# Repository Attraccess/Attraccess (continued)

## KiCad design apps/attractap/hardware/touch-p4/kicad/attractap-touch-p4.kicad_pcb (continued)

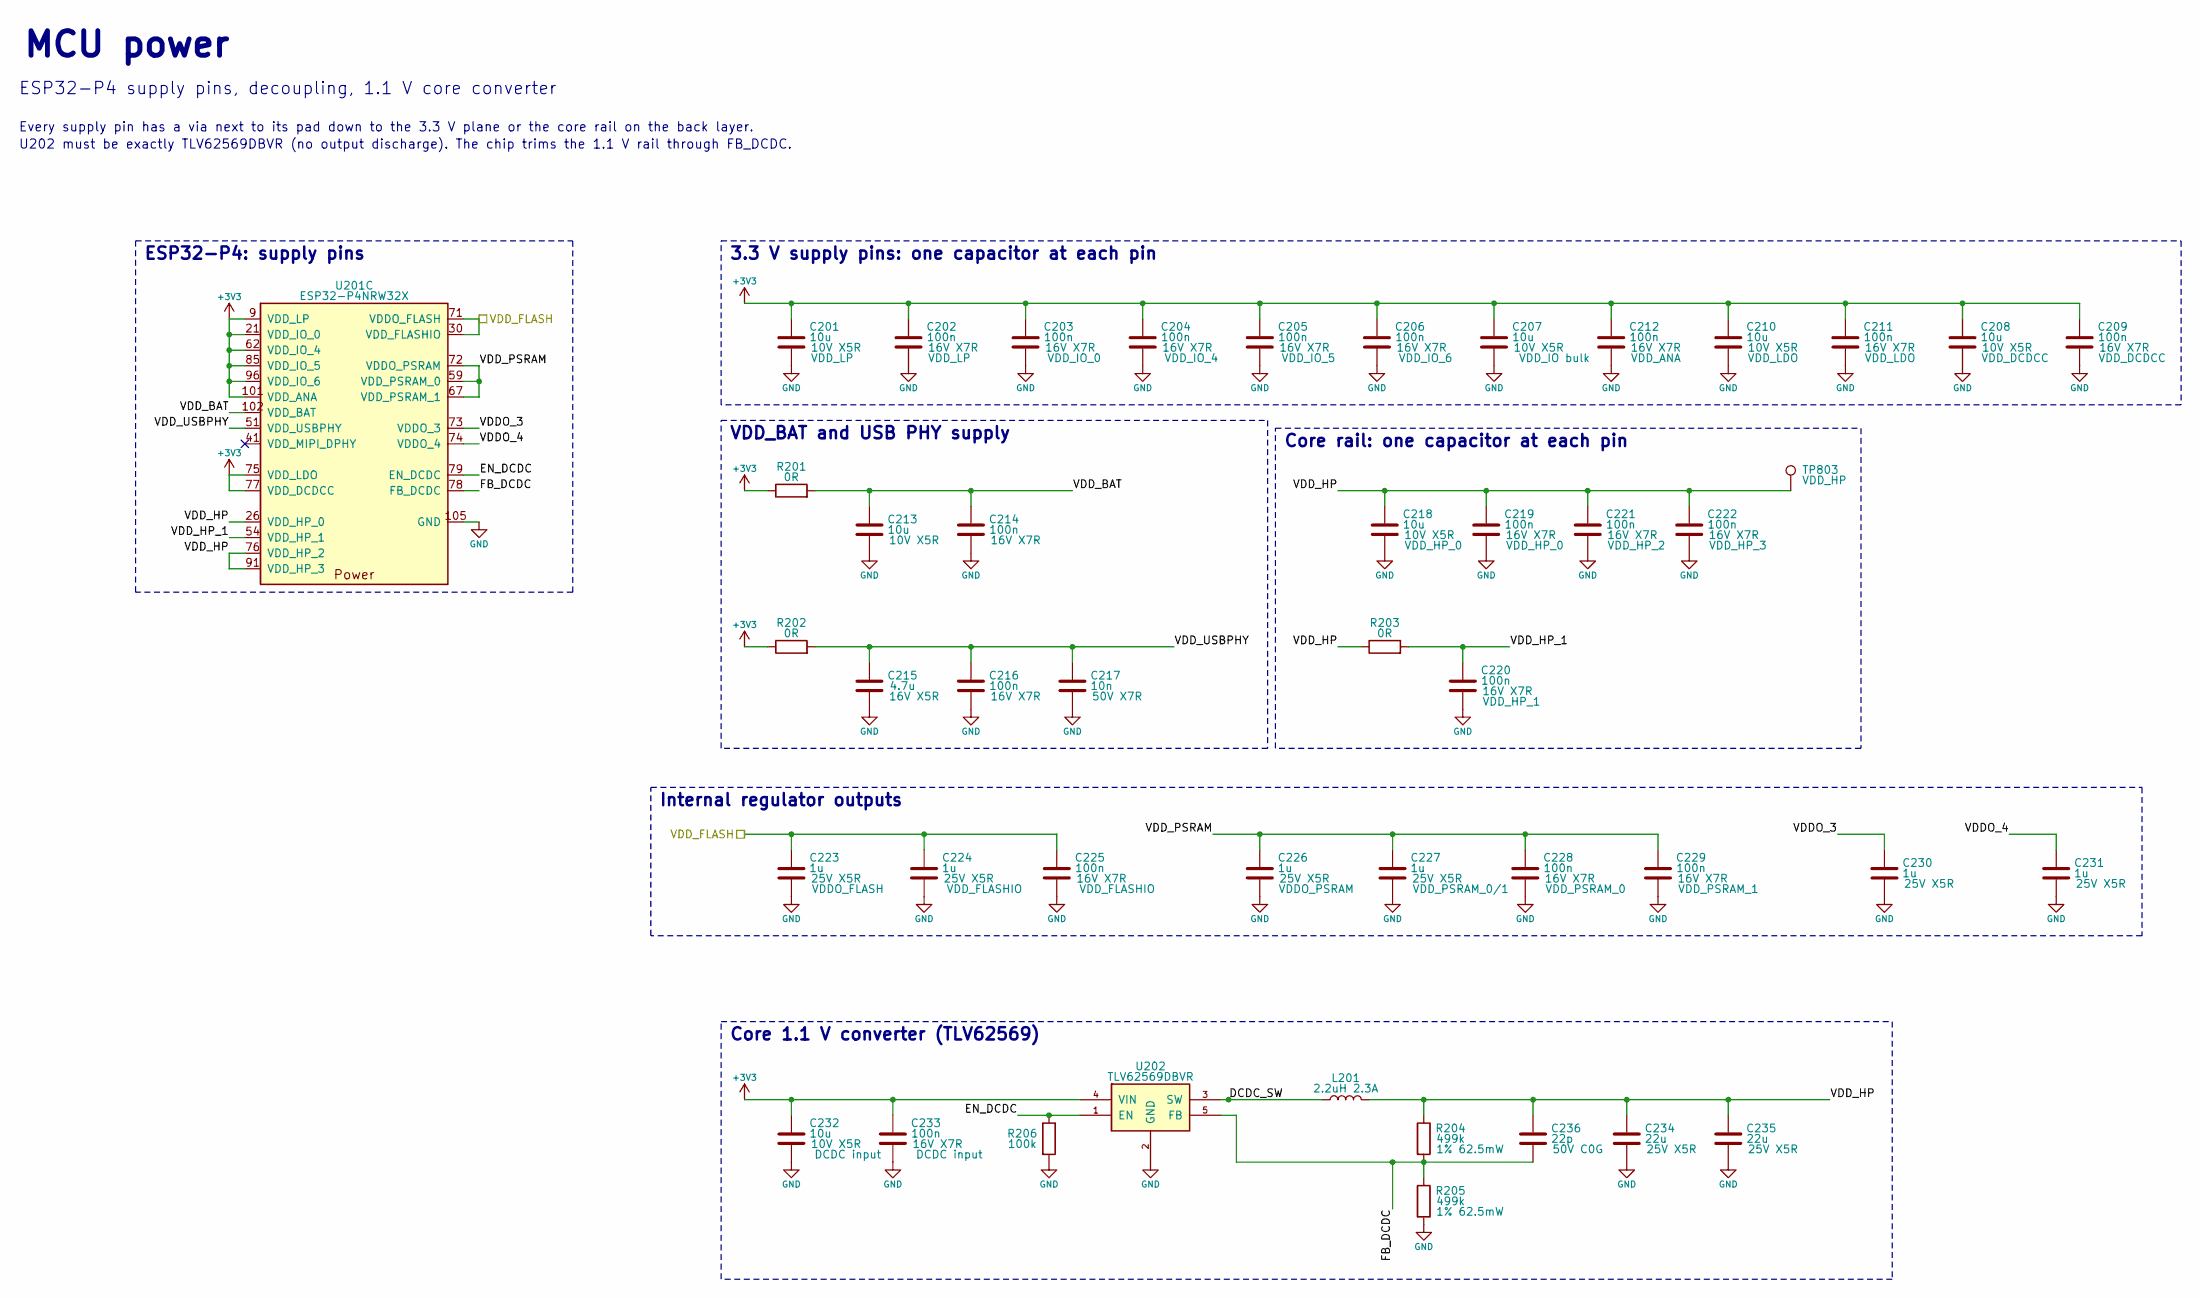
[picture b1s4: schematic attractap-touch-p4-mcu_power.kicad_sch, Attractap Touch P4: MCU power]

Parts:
C201, C207, C208, C210, C213, C218, C232: 10u; C_0603_1608Metric; Rating 10V X5R; MPN CL10A106KP8NNNC; LCSC C19702
C202, C203, C204, C205, C206, C209, C211, C212, C214, C216, C219, C220, C221, C222, C225, C228, C229, C233: 100n; C_0402_1005Metric; Rating 16V X7R; MPN CL05B104KO5NNNC; LCSC C1525
C215: 4.7u; C_0603_1608Metric; Rating 16V X5R; MPN CL10A475KO8NNNC; LCSC C19666
C217: 10n; C_0402_1005Metric; Rating 50V X7R; MPN CL05B103KB5NNNC; LCSC C15195
C223, C224, C226, C227, C230, C231: 1u; C_0402_1005Metric; Rating 25V X5R; MPN CL05A105KA5NQNC; LCSC C52923
C234, C235: 22u; C_0805_2012Metric; Rating 25V X5R; MPN CL21A226MAQNNNE; LCSC C45783
C236: 22p; C_0402_1005Metric; Rating 50V C0G; MPN 0402CG220J500NT; LCSC C1555
L201: 2.2uH 2.3A; IND-SMD_L2.5-W2.0_CKCSA252012; MPN CKCSA252012-2.2uH/M; LCSC C354540
R201, R202, R203: 0R; R_0402_1005Metric; Rating jumper 62.5mW; MPN 0402WGF0000TCE; LCSC C17168
R204, R205: 499k; R_0402_1005Metric; Rating 1% 62.5mW; MPN 0402WGF4993TCE; LCSC C25793
R206: 100k; R_0402_1005Metric; Rating 1% 62.5mW; MPN 0402WGF1003TCE; LCSC C25741
TP803: VDD_HP; TestPoint_Pad_D1.5mm
U201: ESP32-P4NRW32X; QFN-104_L10.0-W10.0-P0.35-TL-EP7.5; MPN ESP32-P4NRW32X; LCSC C54540373
U202: TLV62569DBVR; SOT-23-5_L3.0-W1.7-P0.95-LS2.8-BR; MPN TLV62569DBVR; LCSC C141836

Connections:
+3V3: C201.1, C202.1, C203.1, C204.1, C205.1, C206.1, C207.1, C208.1, C209.1, C210.1, C211.1, C212.1, C232.1, C233.1, R201.1, R202.1, U201.9 (VDD_LP), U201.21 (VDD_IO_0), U201.62 (VDD_IO_4), U201.75 (VDD_LDO), U201.77 (VDD_DCDCC), U201.85 (VDD_IO_5), U201.96 (VDD_IO_6), U201.101 (VDD_ANA), U202.4 (VIN); also elsewhere on the board
/MCU_Power/DCDC_SW: L201.1, U202.3 (SW)
/MCU_Power/EN_DCDC: R206.1, U201.79 (EN_DCDC), U202.1 (EN)
/MCU_Power/FB_DCDC: C236.2, R204.2, R205.1, U201.78 (FB_DCDC), U202.5 (FB)
/MCU_Power/VDDO_3: C230.1, U201.73 (VDDO_3)
/MCU_Power/VDDO_4: C231.1, U201.74 (VDDO_4)
/MCU_Power/VDD_BAT: C213.1, C214.1, R201.2, U201.102 (VDD_BAT)
/MCU_Power/VDD_HP: C218.1, C219.1, C221.1, C222.1, C234.1, C235.1, C236.1, L201.2, R203.1, R204.1, TP803.1, U201.26 (VDD_HP_0), U201.76 (VDD_HP_2), U201.91 (VDD_HP_3)
/MCU_Power/VDD_HP_1: C220.1, R203.2, U201.54 (VDD_HP_1)
/MCU_Power/VDD_PSRAM: C226.1, C227.1, C228.1, C229.1, U201.59 (VDD_PSRAM_0), U201.67 (VDD_PSRAM_1), U201.72 (VDDO_PSRAM)
/MCU_Power/VDD_USBPHY: C215.1, C216.1, C217.1, R202.2, U201.51 (VDD_USBPHY)
/VDD_FLASH: C223.1, C224.1, C225.1, U201.30 (VDD_FLASHIO), U201.71 (VDDO_FLASH); also elsewhere on the board
GND: C201.2, C202.2, C203.2, C204.2, C205.2, C206.2, C207.2, C208.2, C209.2, C210.2, C211.2, C212.2, C213.2, C214.2, C215.2, C216.2, C217.2, C218.2, C219.2, C220.2, C221.2, C222.2, C223.2, C224.2, C225.2, C226.2, C227.2, C228.2, C229.2, C230.2, C231.2, C232.2, C233.2, C234.2, C235.2, R205.2, R206.2, U201.105 (GND), U202.2 (GND); also elsewhere on the board

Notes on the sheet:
MCU power
ESP32-P4 supply pins, decoupling, 1.1 V core converter
Every supply pin has a via next to its pad down to the 3.3 V plane or the core rail on the back layer.
U202 must be exactly TLV62569DBVR (no output discharge). The chip trims the 1.1 V rail through FB_DCDC.
ESP32-P4: supply pins
3.3 V supply pins: one capacitor at each pin
VDD_BAT and USB PHY supply
Core rail: one capacitor at each pin
Internal regulator outputs
Core 1.1 V converter (TLV62569)

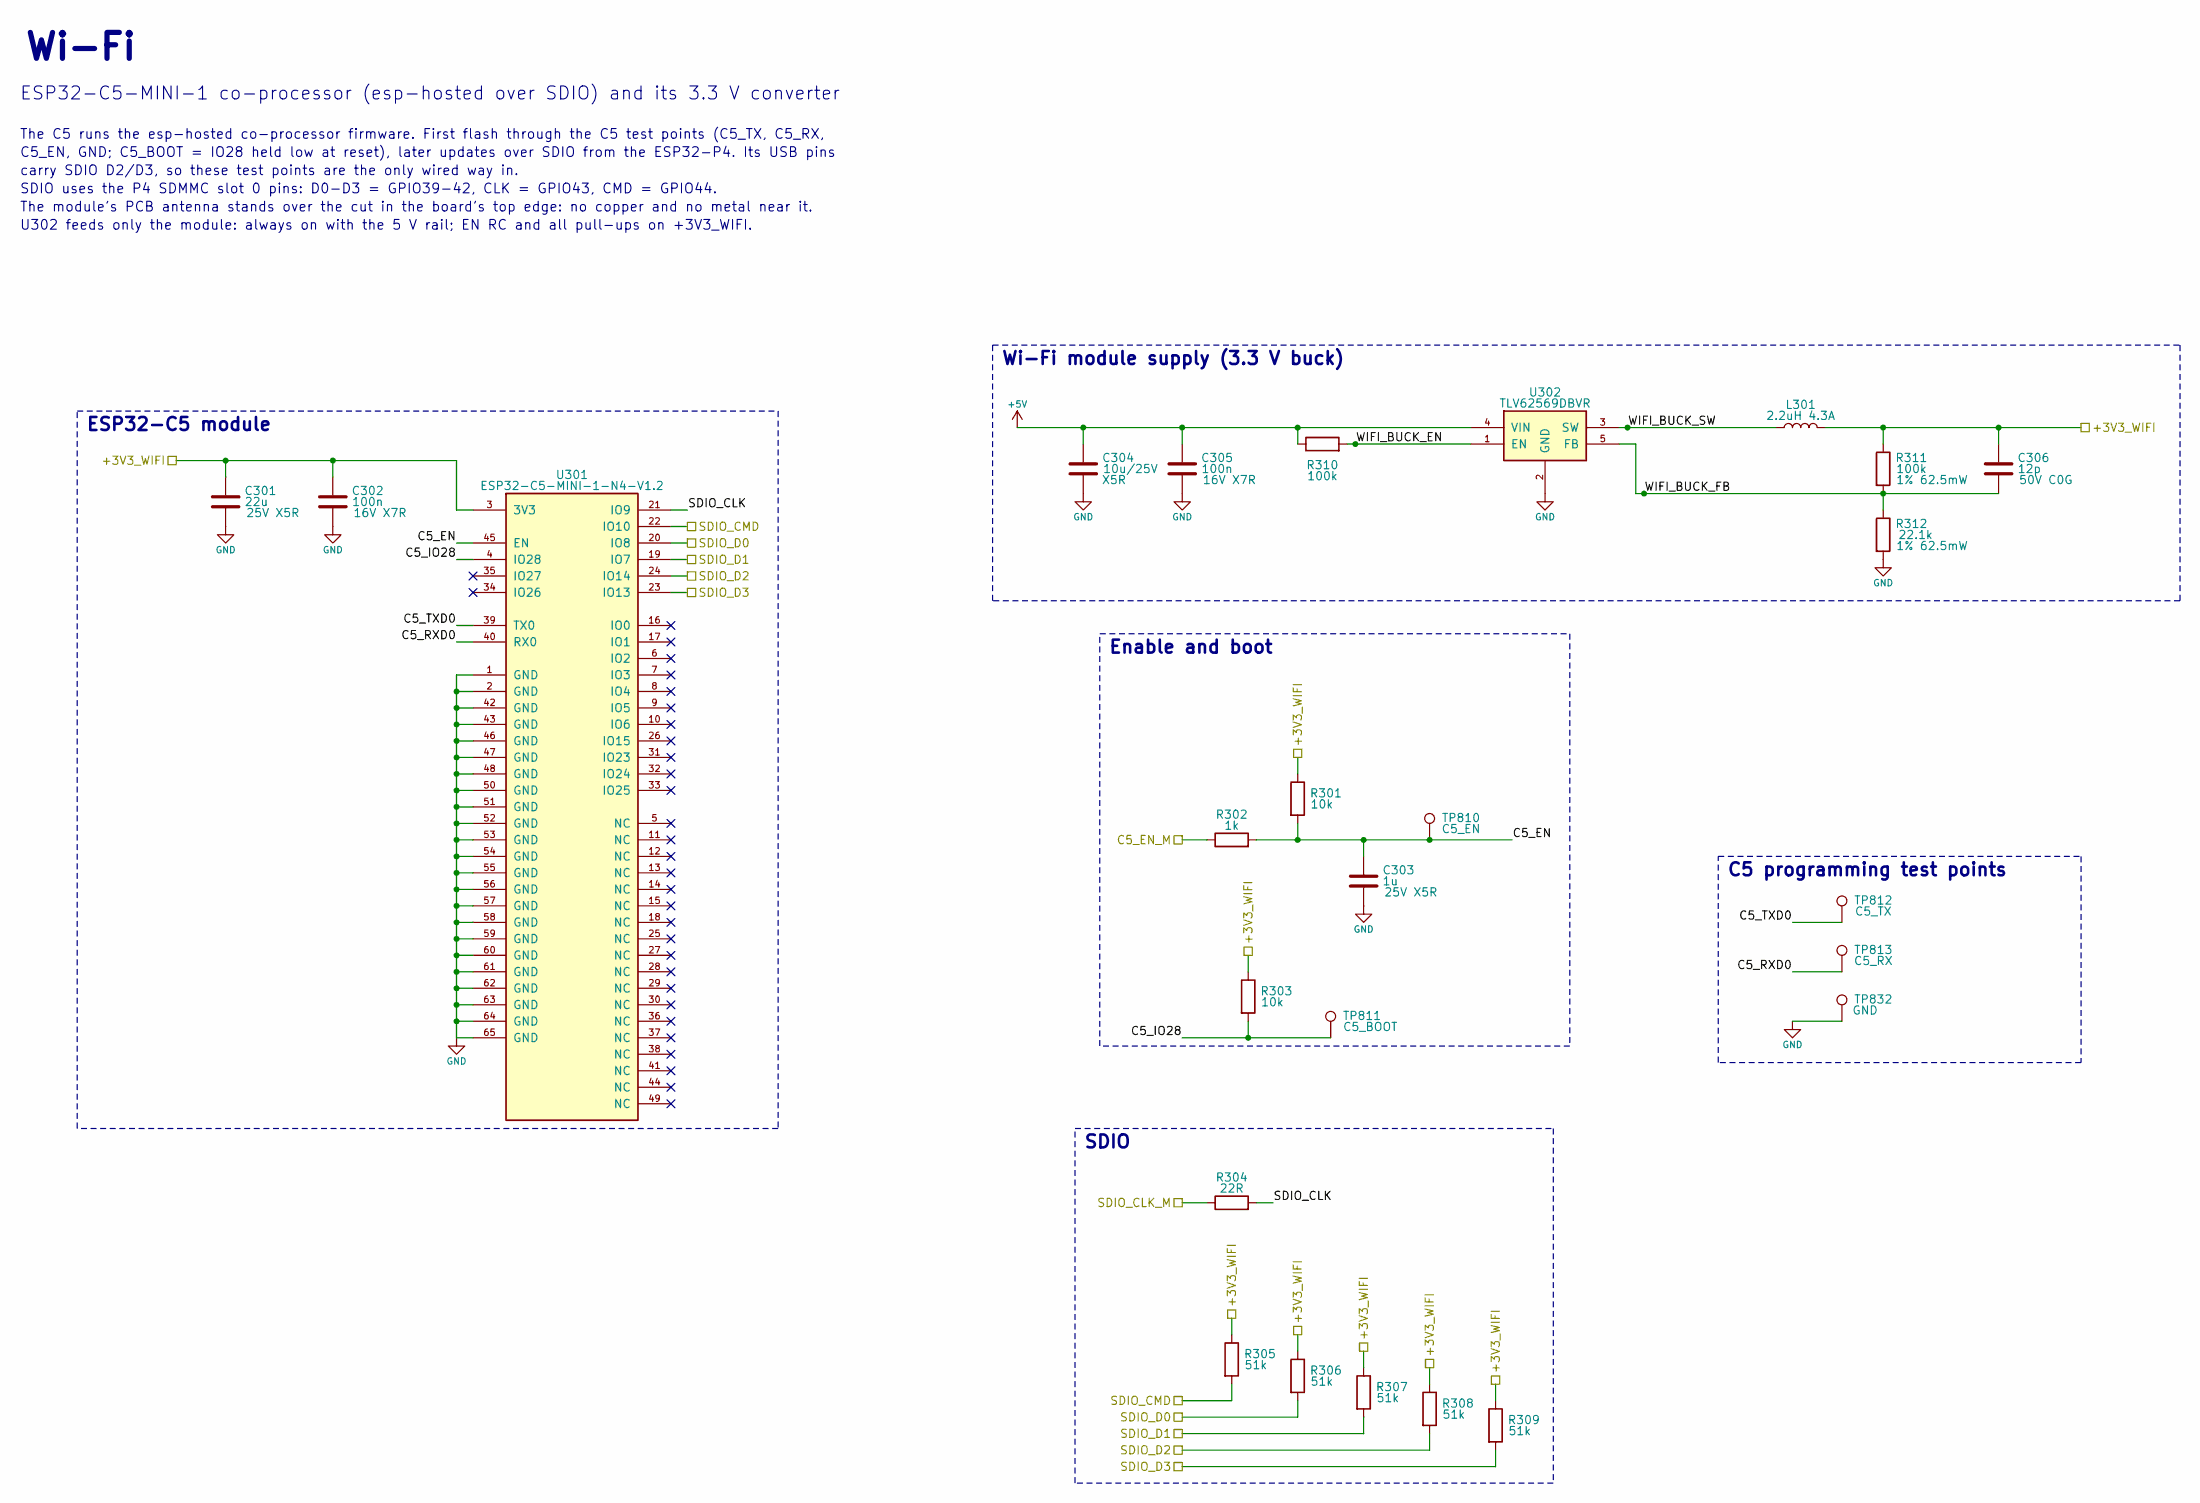
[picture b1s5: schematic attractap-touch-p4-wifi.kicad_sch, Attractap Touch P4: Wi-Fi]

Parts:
C301: 22u; C_0805_2012Metric; Rating 25V X5R; MPN CL21A226MAQNNNE; LCSC C45783
C302, C305: 100n; C_0402_1005Metric; Rating 16V X7R; MPN CL05B104KO5NNNC; LCSC C1525
C303: 1u; C_0402_1005Metric; Rating 25V X5R; MPN CL05A105KA5NQNC; LCSC C52923
C304: 10u/25V; C_0805_2012Metric; Rating X5R; MPN CL21A106KAYNNNE; LCSC C15850
C306: 12p; C_0402_1005Metric; Rating 50V C0G; MPN 0402CG120J500NT; LCSC C1547
L301: 2.2uH 4.3A; IND-SMD_L4.0-W4.0; MPN WPN4020H2R2MT; LCSC C98361
R301, R303: 10k; R_0402_1005Metric; Rating 1% 62.5mW; MPN 0402WGF1002TCE; LCSC C25744
R302: 1k; R_0402_1005Metric; Rating 1% 62.5mW; MPN 0402WGF1001TCE; LCSC C11702
R304: 22R; R_0402_1005Metric; Rating 1% 62.5mW; MPN 0402WGF220JTCE; LCSC C25092
R305, R306, R307, R308, R309: 51k; R_0402_1005Metric; Rating 1% 62.5mW; MPN 0402WGF5102TCE; LCSC C25794
R310, R311: 100k; R_0402_1005Metric; Rating 1% 62.5mW; MPN 0402WGF1003TCE; LCSC C25741
R312: 22.1k; R_0402_1005Metric; Rating 1% 62.5mW; MPN 0402WGF2212TCE; LCSC C43473
TP810: C5_EN; TestPoint_Pad_D1.5mm
TP811: C5_BOOT; TestPoint_Pad_D1.5mm
TP812: C5_TX; TestPoint_Pad_D1.5mm
TP813: C5_RX; TestPoint_Pad_D1.5mm
TP832: GND; TestPoint_Pad_D1.5mm
U301: ESP32-C5-MINI-1-N4-V1.2; CONN-SMD_ESP32-C5-MINI-1-N4; MPN ESP32-C5-MINI-1-N4-V1.2; LCSC C54951860
U302: TLV62569DBVR; SOT-23-5_L3.0-W1.7-P0.95-LS2.8-BR; MPN TLV62569DBVR; LCSC C141836

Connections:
+5V: C304.1, C305.1, R310.1, U302.4 (VIN); also elsewhere on the board
/+3V3_WIFI: C301.1, C302.1, C306.1, L301.2, R301.1, R303.1, R305.1, R306.1, R307.1, R308.1, R309.1, R311.1, U301.3 (3V3); also elsewhere on the board
/C5_EN_M: R302.1; also elsewhere on the board
/SDIO_CLK_M: R304.1; also elsewhere on the board
/SDIO_CMD: R305.2, U301.22 (IO10); also elsewhere on the board
/SDIO_D0: R306.2, U301.20 (IO8); also elsewhere on the board
/SDIO_D1: R307.2, U301.19 (IO7); also elsewhere on the board
/SDIO_D2: R308.2, U301.24 (IO14); also elsewhere on the board
/SDIO_D3: R309.2, U301.23 (IO13); also elsewhere on the board
/WiFi/C5_EN: C303.1, R301.2, R302.2, TP810.1, U301.45 (EN)
/WiFi/C5_IO28: R303.2, TP811.1, U301.4 (IO28)
/WiFi/C5_RXD0: TP813.1, U301.40 (RX0)
/WiFi/C5_TXD0: TP812.1, U301.39 (TX0)
/WiFi/SDIO_CLK: R304.2, U301.21 (IO9)
/WiFi/WIFI_BUCK_EN: R310.2, U302.1 (EN)
/WiFi/WIFI_BUCK_FB: C306.2, R311.2, R312.1, U302.5 (FB)
/WiFi/WIFI_BUCK_SW: L301.1, U302.3 (SW)
GND: C301.2, C302.2, C303.2, C304.2, C305.2, R312.2, TP832.1, U301.1 (GND), U301.2 (GND), U301.42 (GND), U301.43 (GND), U301.46 (GND), U301.47 (GND), U301.48 (GND), U301.50 (GND), U301.51 (GND), U301.52 (GND), U301.53 (GND), U301.54 (GND), U301.55 (GND), U301.56 (GND), U301.57 (GND), U301.58 (GND), U301.59 (GND), U301.60 (GND), U301.61 (GND), U301.62 (GND), U301.63 (GND), U301.64 (GND), U301.65 (GND), U302.2 (GND); also elsewhere on the board

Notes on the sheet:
Wi-Fi
ESP32-C5-MINI-1 co-processor (esp-hosted over SDIO) and its 3.3 V converter
The C5 runs the esp-hosted co-processor firmware. First flash through the C5 test points (C5_TX, C5_RX,
C5_EN, GND; C5_BOOT = IO28 held low at reset), later updates over SDIO from the ESP32-P4. Its USB pins
carry SDIO D2/D3, so these test points are the only wired way in.
SDIO uses the P4 SDMMC slot 0 pins: D0-D3 = GPIO39-42, CLK = GPIO43, CMD = GPIO44.
The module's PCB antenna stands over the cut in the board's top edge: no copper and no metal near it.
U302 feeds only the module: always on with the 5 V rail; EN RC and all pull-ups on +3V3_WIFI.
Wi-Fi module supply (3.3 V buck)
ESP32-C5 module
Enable and boot
SDIO
C5 programming test points

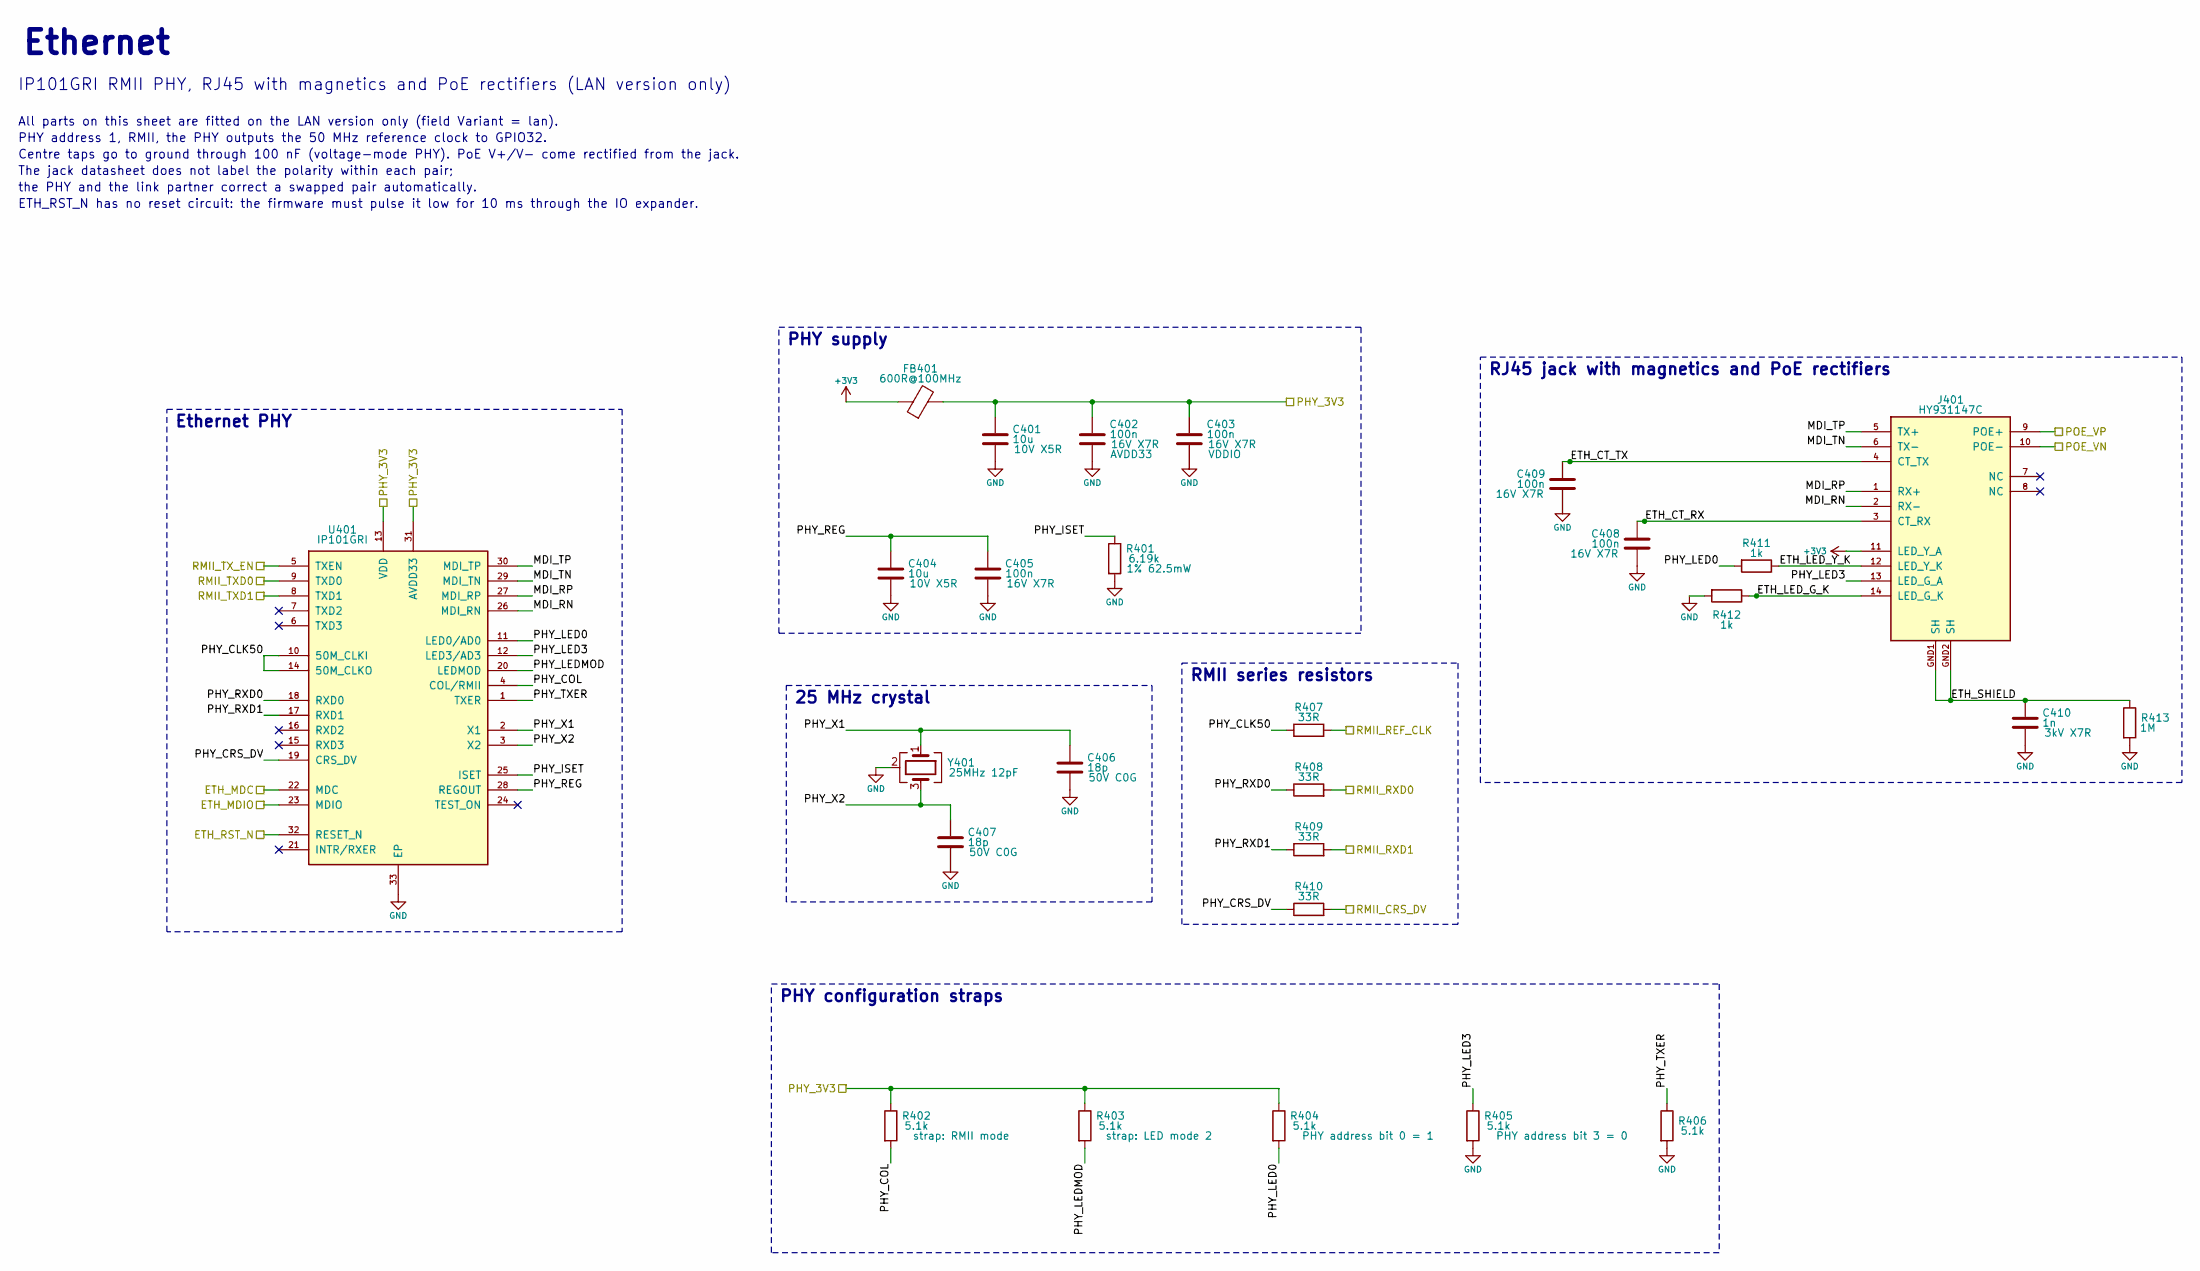
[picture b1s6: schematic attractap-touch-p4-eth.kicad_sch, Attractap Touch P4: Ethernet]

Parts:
C401, C404: 10u; C_0603_1608Metric; Rating 10V X5R; MPN CL10A106KP8NNNC; LCSC C19702
C402, C403, C405, C408, C409: 100n; C_0402_1005Metric; Rating 16V X7R; MPN CL05B104KO5NNNC; LCSC C1525
C406, C407: 18p; C_0402_1005Metric; Rating 50V C0G; MPN 0402CG180J500NT; LCSC C1549
C410: 1n; C_1808_4520Metric; Rating 3kV X7R; MPN 1808B102K302NT; LCSC C967608
FB401: 600R@100MHz; L0603; MPN BLM18KG601SN1D; LCSC C85833
J401: HY931147C; RJ45-TH_HY931147C; MPN HY931147C; LCSC C91754
R401: 6.19k; R_0402_1005Metric; Rating 1% 62.5mW; MPN 0402WGF6191TCE; LCSC C25914
R402, R403, R404, R405, R406: 5.1k; R_0402_1005Metric; Rating 1% 62.5mW; MPN 0402WGF5101TCE; LCSC C25905
R407, R408, R409, R410: 33R; R_0402_1005Metric; Rating 1% 62.5mW; MPN 0402WGF330JTCE; LCSC C25105
R411, R412: 1k; R_0402_1005Metric; Rating 1% 62.5mW; MPN 0402WGF1001TCE; LCSC C11702
R413: 1M; R_1206_3216Metric; Rating 1% 0.25W; MPN 1206W4F1004T5E; LCSC C17927
U401: IP101GRI; QFN-32_L4.0-W4.0-P0.40-BL-EP2.7; MPN IP101GRI; LCSC C703537
Y401: 25MHz 12pF; CRYSTAL-SMD_4P-L3.2-W2.5-BL; MPN X322525MOB4SI; LCSC C9006

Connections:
+3V3: FB401.1, J401.11 (LED_Y_A); also elsewhere on the board
/ETH_MDC: U401.22 (MDC); also elsewhere on the board
/ETH_MDIO: U401.23 (MDIO); also elsewhere on the board
/ETH_RST_N: U401.32 (RESET_N); also elsewhere on the board
/Ethernet/ETH_CT_RX: C408.1, J401.3 (CT_RX)
/Ethernet/ETH_CT_TX: C409.1, J401.4 (CT_TX)
/Ethernet/ETH_LED_G_K: J401.14 (LED_G_K), R412.1
/Ethernet/ETH_LED_Y_K: J401.12 (LED_Y_K), R411.1
/Ethernet/ETH_SHIELD: C410.1, J401.GND1 (SH), J401.GND2 (SH), R413.1
/Ethernet/MDI_RN: J401.2 (RX-), U401.26 (MDI_RN)
/Ethernet/MDI_RP: J401.1 (RX+), U401.27 (MDI_RP)
/Ethernet/MDI_TN: J401.6 (TX-), U401.29 (MDI_TN)
/Ethernet/MDI_TP: J401.5 (TX+), U401.30 (MDI_TP)
/Ethernet/PHY_CLK50: R407.1, U401.10 (50M_CLKI), U401.14 (50M_CLKO)
/Ethernet/PHY_COL: R402.2, U401.4 (COL/RMII)
/Ethernet/PHY_CRS_DV: R410.1, U401.19 (CRS_DV)
/Ethernet/PHY_ISET: R401.1, U401.25 (ISET)
/Ethernet/PHY_LED0: R404.2, R411.2, U401.11 (LED0/AD0)
/Ethernet/PHY_LED3: J401.13 (LED_G_A), R405.1, U401.12 (LED3/AD3)
/Ethernet/PHY_LEDMOD: R403.2, U401.20 (LEDMOD)
/Ethernet/PHY_REG: C404.1, C405.1, U401.28 (REGOUT)
/Ethernet/PHY_RXD0: R408.1, U401.18 (RXD0)
/Ethernet/PHY_RXD1: R409.1, U401.17 (RXD1)
/Ethernet/PHY_TXER: R406.1, U401.1 (TXER)
/Ethernet/PHY_X1: C406.1, U401.2 (X1), Y401.1
/Ethernet/PHY_X2: C407.1, U401.3 (X2), Y401.3
/PHY_3V3: C401.1, C402.1, C403.1, FB401.2, R402.1, R403.1, R404.1, U401.13 (VDD), U401.31 (AVDD33); also elsewhere on the board
/POE_VN: J401.10 (POE-); also elsewhere on the board
/POE_VP: J401.9 (POE+); also elsewhere on the board
/RMII_CRS_DV: R410.2; also elsewhere on the board
/RMII_REF_CLK: R407.2; also elsewhere on the board
/RMII_RXD0: R408.2; also elsewhere on the board
/RMII_RXD1: R409.2; also elsewhere on the board
/RMII_TXD0: U401.9 (TXD0); also elsewhere on the board
/RMII_TXD1: U401.8 (TXD1); also elsewhere on the board
/RMII_TX_EN: U401.5 (TXEN); also elsewhere on the board
GND: C401.2, C402.2, C403.2, C404.2, C405.2, C406.2, C407.2, C408.2, C409.2, C410.2, R401.2, R405.2, R406.2, R412.2, R413.2, U401.33 (EP), Y401.2 (G), Y401.4 (G); also elsewhere on the board

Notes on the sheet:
Ethernet
IP101GRI RMII PHY, RJ45 with magnetics and PoE rectifiers (LAN version only)
All parts on this sheet are fitted on the LAN version only (field Variant = lan).
PHY address 1, RMII, the PHY outputs the 50 MHz reference clock to GPIO32.
Centre taps go to ground through 100 nF (voltage-mode PHY). PoE V+/V- come rectified from the jack.
The jack datasheet does not label the polarity within each pair;
the PHY and the link partner correct a swapped pair automatically.
ETH_RST_N has no reset circuit: the firmware must pulse it low for 10 ms through the IO expander.
Ethernet PHY
PHY supply
25 MHz crystal
PHY configuration straps
RMII series resistors
RJ45 jack with magnetics and PoE rectifiers

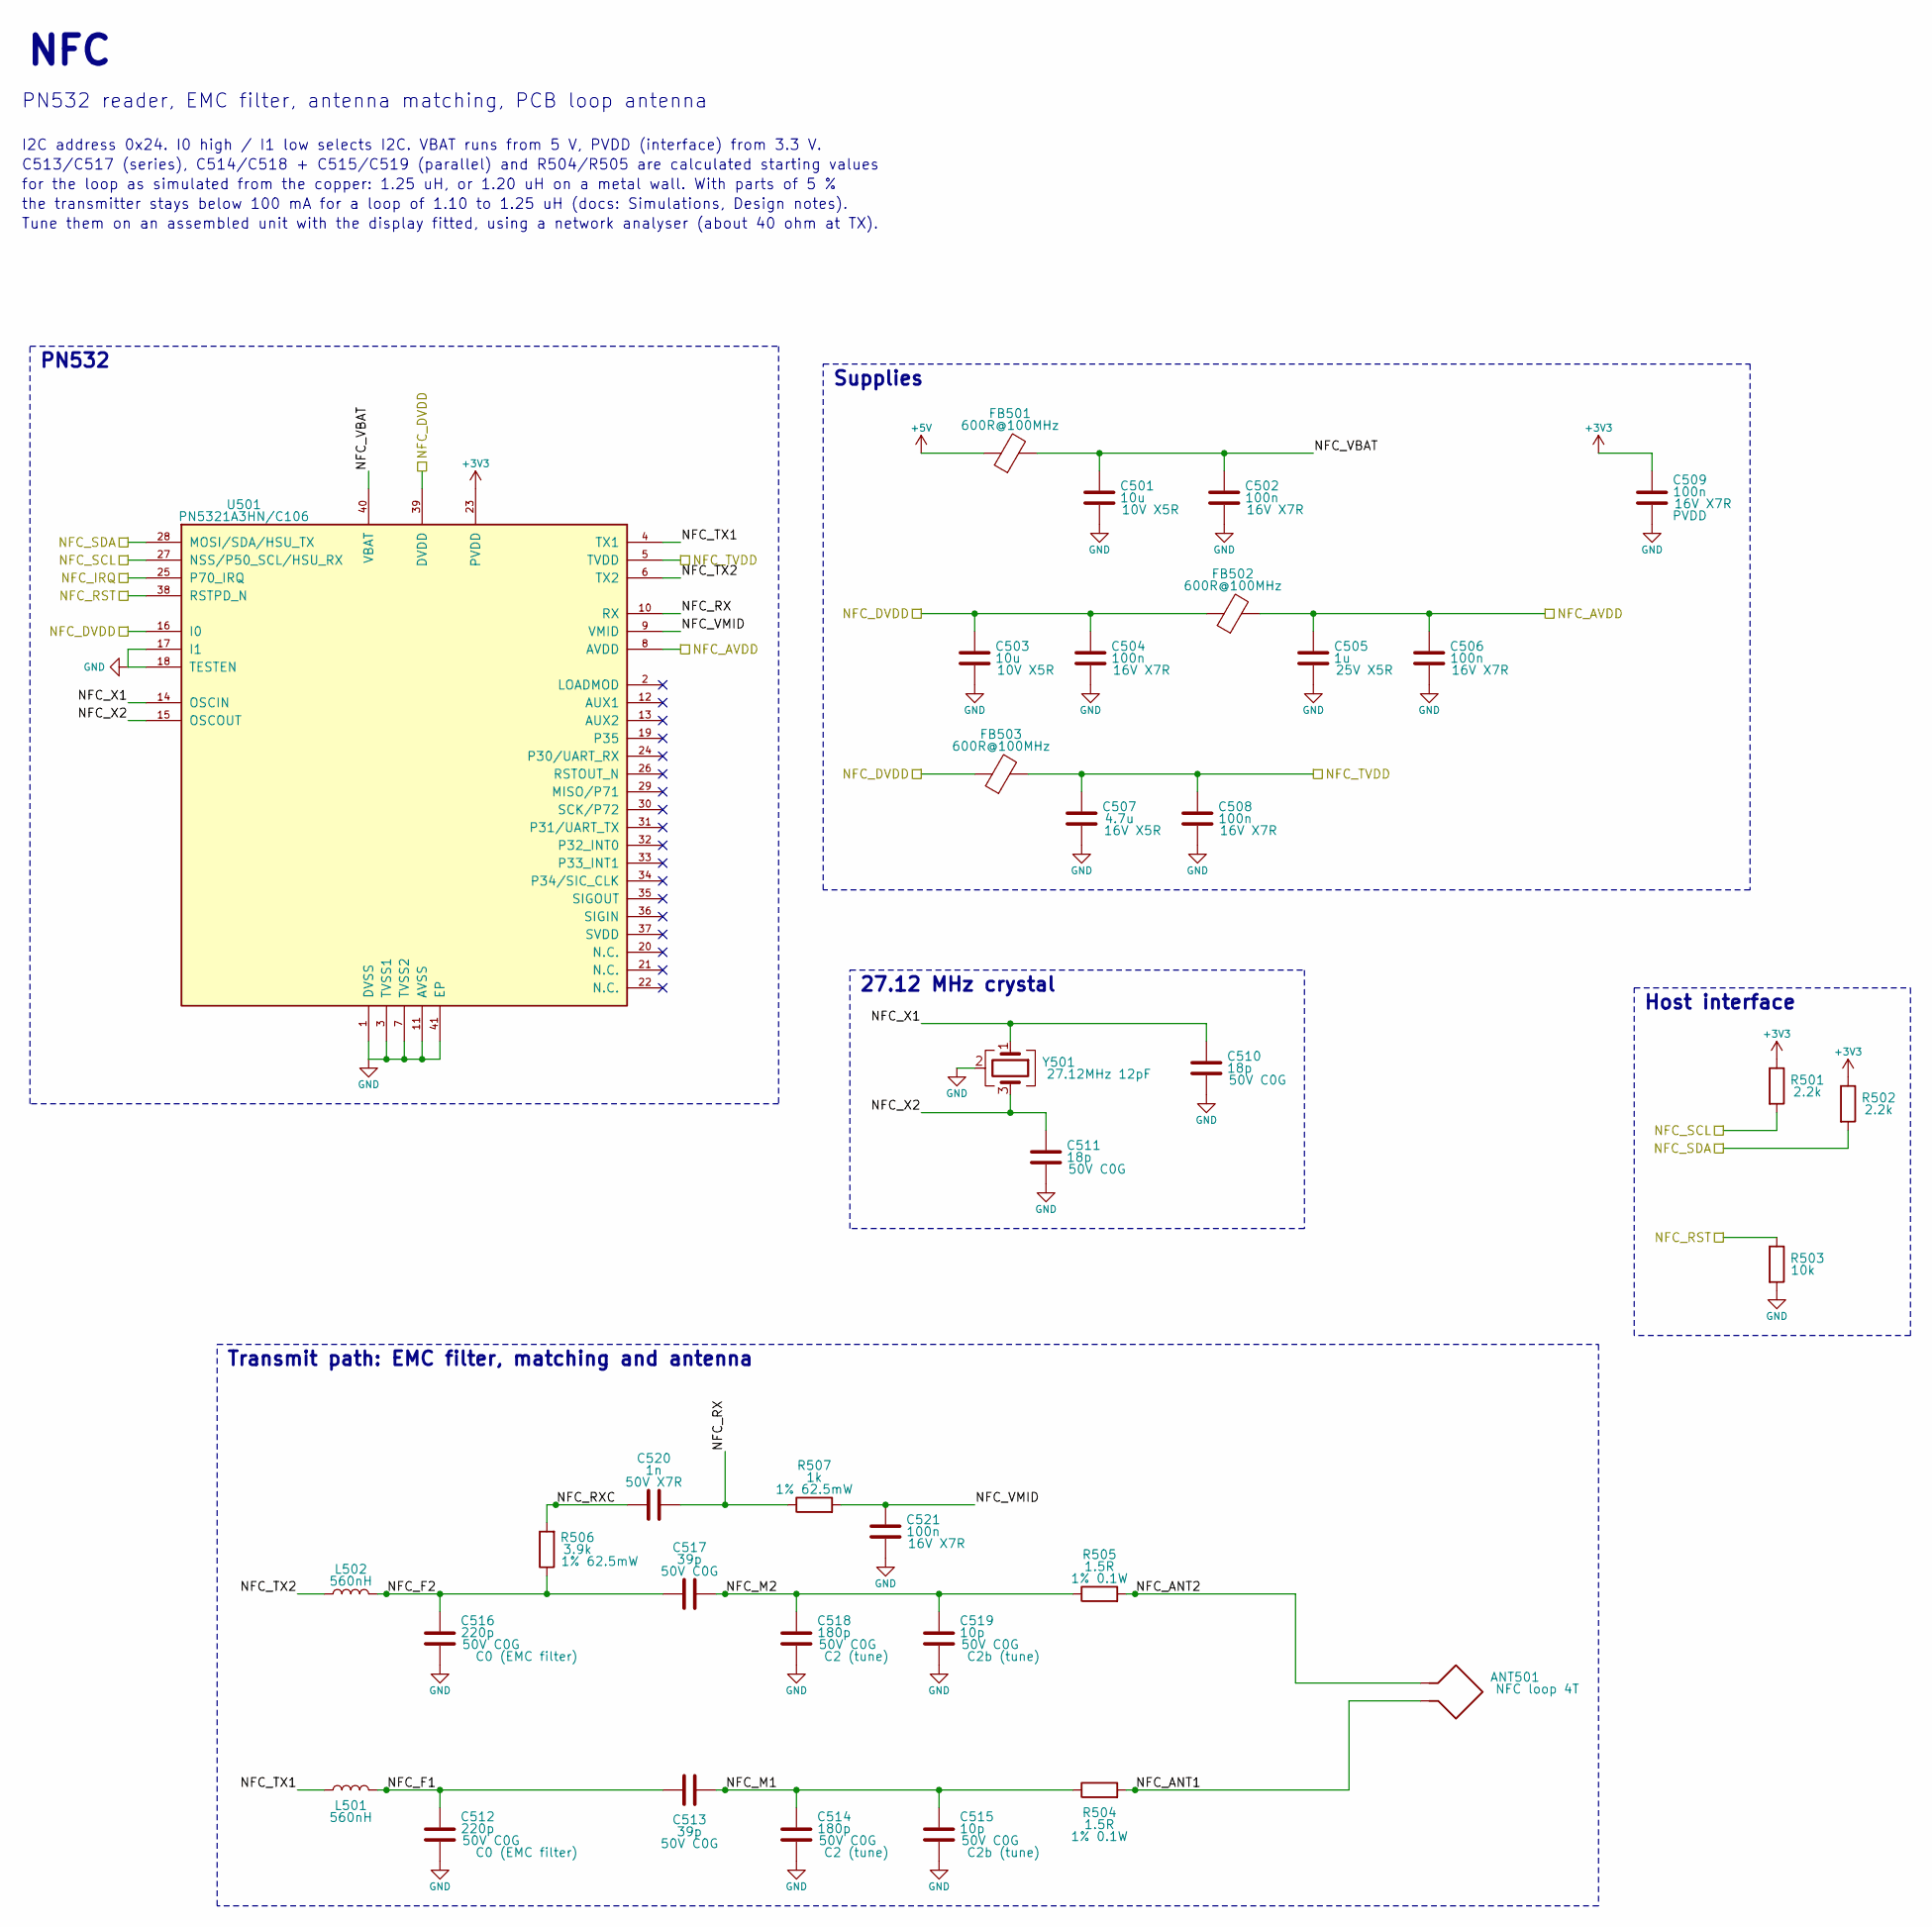
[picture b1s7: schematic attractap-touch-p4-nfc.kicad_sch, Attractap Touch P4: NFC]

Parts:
ANT501: NFC loop 4T; NFC_Antenna_4T
C501, C503: 10u; C_0603_1608Metric; Rating 10V X5R; MPN CL10A106KP8NNNC; LCSC C19702
C502, C504, C506, C508, C509, C521: 100n; C_0402_1005Metric; Rating 16V X7R; MPN CL05B104KO5NNNC; LCSC C1525
C505: 1u; C_0402_1005Metric; Rating 25V X5R; MPN CL05A105KA5NQNC; LCSC C52923
C507: 4.7u; C_0603_1608Metric; Rating 16V X5R; MPN CL10A475KO8NNNC; LCSC C19666
C510, C511: 18p; C_0402_1005Metric; Rating 50V C0G; MPN 0402CG180J500NT; LCSC C1549
C512, C516: 220p; C_0402_1005Metric; Rating 50V C0G; MPN GRM1555C1H221JA01D; LCSC C71693
C513, C517: 39p; C_0402_1005Metric; Rating 50V C0G; MPN CC0402JRNPO9BN390; LCSC C106223
C514, C518: 180p; C_0402_1005Metric; Rating 50V C0G; MPN CC0402JRNPO9BN181; LCSC C106999
C515, C519: 10p; C_0402_1005Metric; Rating 50V C0G; MPN CL05C100JB5NNNC; LCSC C32949
C520: 1n; C_0402_1005Metric; Rating 50V X7R; MPN 0402B102K500NT; LCSC C1523
FB501, FB502, FB503: 600R@100MHz; L0603; MPN BLM18KG601SN1D; LCSC C85833
L501, L502: 560nH; IND-SMD_L1.6-W0.8-1; MPN LQW18CNR56J00D; LCSC C91630
R501, R502: 2.2k; R_0402_1005Metric; Rating 1% 62.5mW; MPN 0402WGF2201TCE; LCSC C25879
R503: 10k; R_0402_1005Metric; Rating 1% 62.5mW; MPN 0402WGF1002TCE; LCSC C25744
R504, R505: 1.5R; R_0603_1608Metric; Rating 1% 0.1W; MPN 0603WAF150KT5E; LCSC C22769
R506: 3.9k; R_0402_1005Metric; Rating 1% 62.5mW; MPN 0402WGF3901TCE; LCSC C51721
R507: 1k; R_0402_1005Metric; Rating 1% 62.5mW; MPN 0402WGF1001TCE; LCSC C11702
U501: PN5321A3HN/C106; QFN-40_L6.0-W6.0-P0.50-BL-EP; MPN PN5321A3HN (Tokmas); LCSC C53457895
Y501: 27.12MHz 12pF; CRYSTAL-SMD_4P-L3.2-W2.5-BL; MPN X32252712MOB4SI; LCSC C113669

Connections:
+3V3: C509.1, R501.1, R502.1, U501.23 (PVDD); also elsewhere on the board
+5V: FB501.1; also elsewhere on the board
/NFC/NFC_ANT1: ANT501.2, R504.2
/NFC/NFC_ANT2: ANT501.1, R505.2
/NFC/NFC_F1: C512.1, C513.1, L501.2
/NFC/NFC_F2: C516.1, C517.1, L502.2, R506.1
/NFC/NFC_M1: C513.2, C514.1, C515.1, R504.1
/NFC/NFC_M2: C517.2, C518.1, C519.1, R505.1
/NFC/NFC_RX: C520.2, R507.1, U501.10 (RX)
/NFC/NFC_RXC: C520.1, R506.2
/NFC/NFC_TX1: L501.1, U501.4 (TX1)
/NFC/NFC_TX2: L502.1, U501.6 (TX2)
/NFC/NFC_VBAT: C501.1, C502.1, FB501.2, U501.40 (VBAT)
/NFC/NFC_VMID: C521.1, R507.2, U501.9 (VMID)
/NFC/NFC_X1: C510.1, U501.14 (OSCIN), Y501.1
/NFC/NFC_X2: C511.1, U501.15 (OSCOUT), Y501.3
/NFC_AVDD: C505.1, C506.1, FB502.2, U501.8 (AVDD); also elsewhere on the board
/NFC_DVDD: C503.1, C504.1, FB502.1, FB503.1, U501.16 (I0), U501.39 (DVDD); also elsewhere on the board
/NFC_IRQ: U501.25 (P70_IRQ); also elsewhere on the board
/NFC_RST: R503.1, U501.38 (RSTPD_N); also elsewhere on the board
/NFC_SCL: R501.2, U501.27 (NSS/P50_SCL/HSU_RX); also elsewhere on the board
/NFC_SDA: R502.2, U501.28 (MOSI/SDA/HSU_TX); also elsewhere on the board
/NFC_TVDD: C507.1, C508.1, FB503.2, U501.5 (TVDD); also elsewhere on the board
GND: C501.2, C502.2, C503.2, C504.2, C505.2, C506.2, C507.2, C508.2, C509.2, C510.2, C511.2, C512.2, C514.2, C515.2, C516.2, C518.2, C519.2, C521.2, R503.2, U501.1 (DVSS), U501.3 (TVSS1), U501.7 (TVSS2), U501.11 (AVSS), U501.17 (I1), U501.18 (TESTEN), U501.41 (EP), Y501.2 (G), Y501.4 (G); also elsewhere on the board

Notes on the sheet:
NFC
PN532 reader, EMC filter, antenna matching, PCB loop antenna
I2C address 0x24. I0 high / I1 low selects I2C. VBAT runs from 5 V, PVDD (interface) from 3.3 V.
C513/C517 (series), C514/C518 + C515/C519 (parallel) and R504/R505 are calculated starting values
for the loop as simulated from the copper: 1.25 uH, or 1.20 uH on a metal wall. With parts of 5 %
the transmitter stays below 100 mA for a loop of 1.10 to 1.25 uH (docs: Simulations, Design notes).
Tune them on an assembled unit with the display fitted, using a network analyser (about 40 ohm at TX).
PN532
Supplies
27.12 MHz crystal
Host interface
Transmit path: EMC filter, matching and antenna
